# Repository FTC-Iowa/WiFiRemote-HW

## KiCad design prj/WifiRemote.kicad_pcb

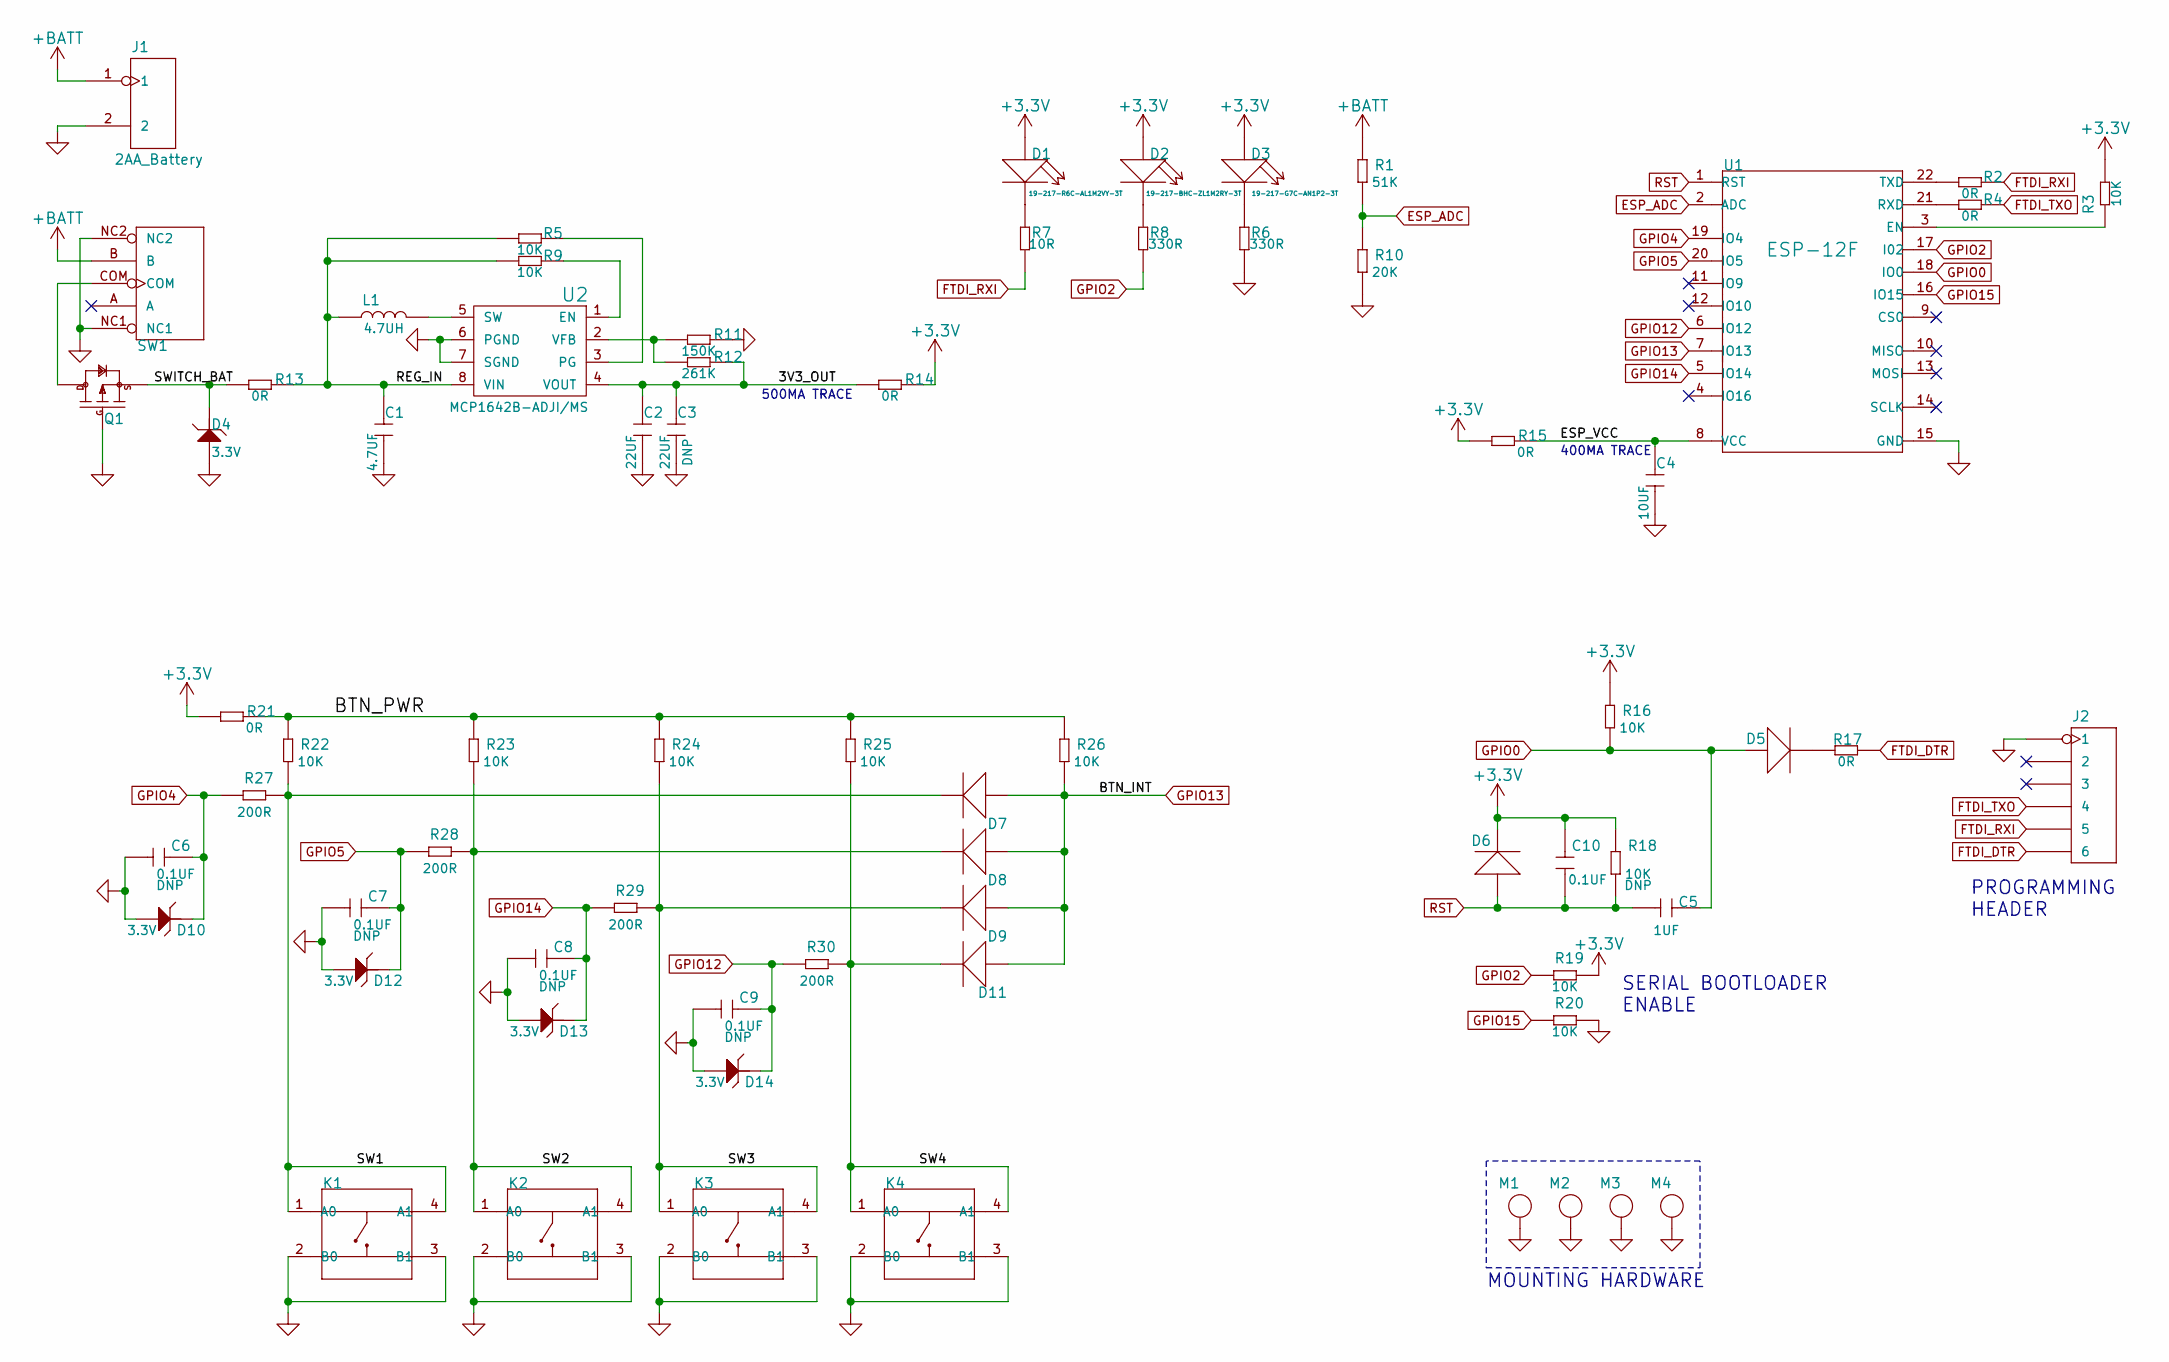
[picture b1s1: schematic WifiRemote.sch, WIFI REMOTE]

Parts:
C1: CERAMIC-4.7UF-10V-10%-X5R_0603_; C0603; MPN CC0603KRX5R6BB475
C2, C3: CERAMIC-22UF-6.3V-20%-X5R_0805_; C0805; MPN CC0805MKX5R5BB226
C4: CERAMIC-10UF-10V-10%-X5R_0603_; C0603; MPN CC0603KRX5R6BB106
C5: CERAMIC-1UF-25V-10%-X7R_0603_; C0603; MPN CC0603KRX7R8BB105
C6, C7, C8, C9, C10: CERAMIC-100NF-50V-10%-X7R_0603_; C0603; MPN CC0603KRX7R9BB104
D1: LED-SMD-RED-DIFFUSED_0603_; LED-0603; MPN 19-217-R6C-AL1M2VY-3T
D2: SMD-LED-CLEAR-BLUE_0603_; LED-0603; MPN 19-217-BHC-ZL1M2RY-3T
D3: SMD-LED-CLEAR-GREEN_0603_; LED-0603; MPN 19-217-G7C-AN1P2-3T
D4, D10, D12, D13, D14: SMD-Diode-TVS-3.3VMW-15V-SOD-523; SOD-523_IMPROVED; MPN CJ;CESD3V3D5
D5, D6, D7, D8, D9, D11: SMD-DIODE-SCHOTTKY-20V-1A_SOD-123_; SOD-123; MPN B5819W
J1: 2AA_Battery; header_1x2; MPN BH-321-1A
J2: DIP-BLACK-MALE-HEADER_6P-2.54_; H6-2.54; MPN P125-1106A1BS116A1
K1, K2, K3, K4: DIP-SWITCH-TACTILE-SPST-NO_TS-1109_4P-D6.0MM_; SW4-6.0X6.0X5.0MM
L1: SMD-Inductor-4.7uH-20%-L0420; ICEE_Inductor_SPD3D16-4R7M; MPN SPD3D16-4R7M
M1, M2, M3, M4: Mechanical_Mount; mounting_panhead6_5mm
Q1: SMD-MOSFET-P-CH-20V-2A-FDN340P_SOT-23_; SOT-23; MPN FDN340P
R1: SMD-RES-51K-5%-1_10W_0603_; R0603; MPN RC0603JR-0751KL
R2, R4, R13, R14, R15, R17, R21: SMD-RES-0R-5%-1_10W_0603_; R0603; MPN RC0603JR-070RL
R3, R16, R18, R19, R20, R22, R23, R24, R25, R26: SMD-RES-10K-5%-1_10W_0603_; R0603; MPN RC0603JR-0710KL
R5, R9: SMD-RES-10K-1%-1_10W_0603_; R0603; MPN RC0603FR-0710KL
R6, R8: SMD-RES-330R-1%-1_10W_0603_; R0603; MPN RC0603FR-07330RL
R7: SMD-RES-10R-5%-1_10W_0603_; R0603; MPN RC0603JR-0710RL
R10: SMD-RES-20K-1%-1_10W_0603_; R0603; MPN RC0603FR-0720KL
R11: SMD-RES-150K-1%-1_10W_0603_; R0603; MPN RC0603FR-07150KL
R12: SMD-RES-261K-1%-1_10W_0603_; R0603; MPN CRCW0603261KFKEA
R27, R28, R29, R30: SMD-RES-200R-5%-1_10W_0603_; R0603; MPN RC0603JR-07200RL
SW1: DIP-TOGGLE-SWITCH-ON-ON_3+2P-8.8X4.6MM_-90D; SW5-2.0-8.8X4.4X4.7MM-90D; MPN 3P-2.0-90D3P-2.0-90D-REINFORCE
U1: CONTROLLER-ESP8266; ESP-12F_SMT_22PIN; PART NUMBER ESP-12F
U2: BOOST-MCP1642B-ADJI/MC-MSOP8; MSOP-8_3x3mm_Pitch0.65mm; PART NUMBER MCP1642B-ADJI/MS

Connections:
+3V3: C10.1, D1.+, D2.+, D3.+, D6.-, R3.1, R14.1, R15.2, R16.1, R18.1, R19.2, R21.2
+BATT: J1.1, R1.1, SW1.B
/3V3_OUT: C2.1, C3.1, R12.1, R14.2, U2.4 (VOUT)
/BTN_PWR: R21.1, R22.1, R23.1, R24.1, R25.1, R26.1
/ESP_VCC: C4.1, R15.1, U1.8 (VCC)
/REG_IN: C1.1, L1.1, R5.2, R9.2, R13.1, U2.8 (VIN)
/SW1: D7.-, K1.1 (A0), K1.4 (A1), R22.2, R27.2
/SW2: D8.-, K2.1 (A0), K2.4 (A1), R23.2, R28.2
/SW3: D9.-, K3.1 (A0), K3.4 (A1), R24.2, R29.2
/SW4: D11.-, K4.1 (A0), K4.4 (A1), R25.2, R30.2
/SWITCH_BAT: D4.1, Q1.2 (S), R13.2
ESP_ADC: R1.2, R10.1, U1.2 (ADC)
FTDI_DTR: J2.6, R17.1
FTDI_RXI: J2.5, R2.1, R7.2
FTDI_TXO: J2.4, R4.1
GNDD: C1.2, C2.2, C3.2, C4.2, C6.1, C7.1, C8.1, C9.1, D4.2, D10.2, D12.2, D13.2, D14.2, J1.2, J2.1, K1.2 (B0), K1.3 (B1), K2.2 (B0), K2.3 (B1), K3.2 (B0), K3.3 (B1), K4.2 (B0), K4.3 (B1), M1.1, M2.1, M3.1, M4.1, Q1.1 (G), R6.2, R10.2, R11.1, R20.2, SW1.NC1, SW1.NC2, U1.15 (GND), U2.6 (PGND), U2.7 (SGND)
GPIO0: C5.2, D5.+, R16.2, U1.18 (IO0)
GPIO2: R8.2, R19.1, U1.17 (I02)
GPIO4: C6.2, D10.1, R27.1, U1.19 (IO4)
GPIO5: C7.2, D12.1, R28.1, U1.20 (IO5)
GPIO12: C9.2, D14.1, R30.1, U1.6 (IO12)
GPIO13: D7.+, D8.+, D9.+, D11.+, R26.2, U1.7 (IO13)
GPIO14: C8.2, D13.1, R29.1, U1.5 (IO14)
GPIO15: R20.1, U1.16 (IO15)
unnamed: D1.-, R7.1
unnamed: D2.-, R8.1
unnamed: D3.-, R6.1
unnamed: D5.-, R17.2
unnamed: L1.2, U2.5 (SW)
unnamed: Q1.3 (D), SW1.COM
unnamed: R2.2, U1.22 (TXD)
unnamed: R3.2, U1.3 (EN)
unnamed: R4.2, U1.21 (RXD)
unnamed: R5.1, U2.3 (PG)
unnamed: R9.1, U2.1 (EN)
unnamed: R11.2, R12.2, U2.2 (VFB)
RST: C5.1, C10.2, D6.+, R18.2, U1.1 (RST)

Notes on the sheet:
PROGRAMMING HEADER
SERIAL BOOTLOADER ENABLE
500MA TRACE
400MA TRACE
MOUNTING HARDWARE

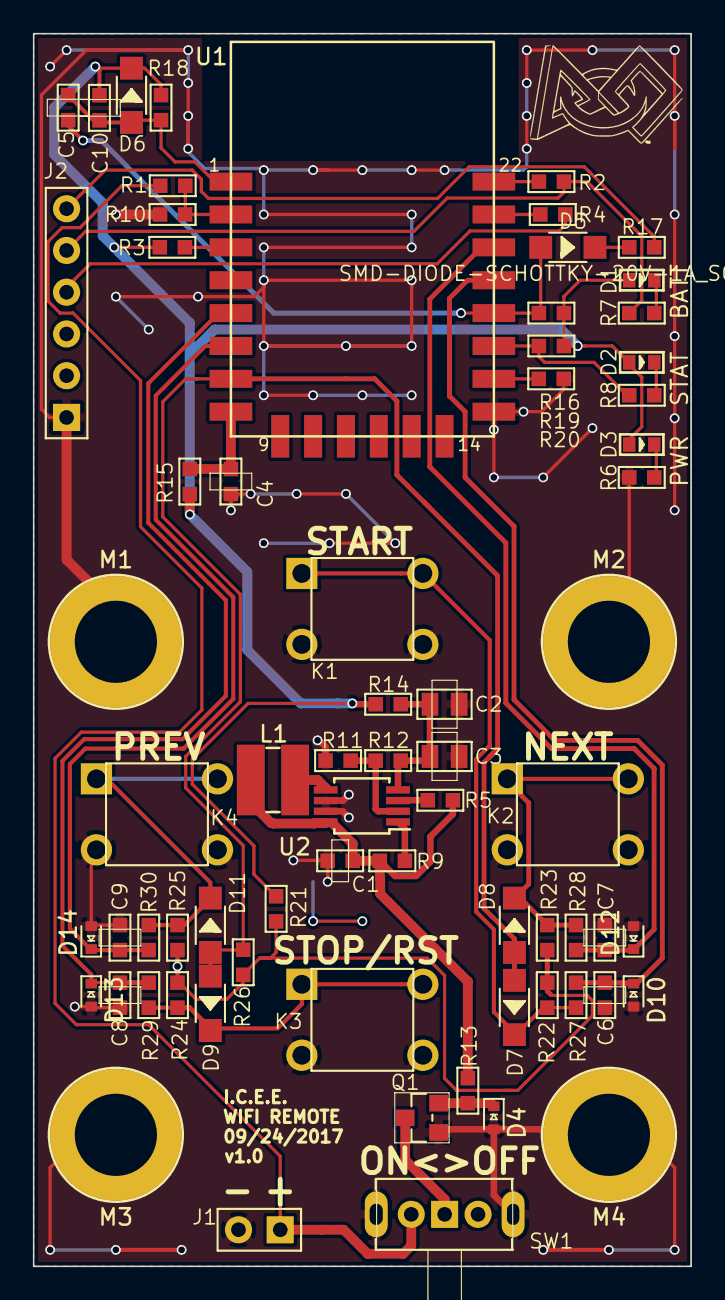
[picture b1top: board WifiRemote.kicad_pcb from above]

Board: 2 copper layers, 40.0 x 75.0 mm, 69 parts (0 on the bottom side), 37 nets.

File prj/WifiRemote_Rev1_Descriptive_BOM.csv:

Component,Description,Part,Designators,Footprint,SKU,MPN,PLACE,Cost,Quantity Per PCB,Cost Per PCB
1,,CERAMIC-100NF-50V-10%-X7R_0603_,C6 C7 C8 C9,C0603,302010138,CC0603KRX7R9BB104,DNP,$0.01 ,4,$0.00 
2,,CERAMIC-10UF-10V-10%-X5R_0603_,C4,C0603,302010103,CC0603KRX5R6BB106,,$0.02 ,1,$0.02 
3,,CERAMIC-1UF-25V-10%-X7R_0603_,C5,C0603,302010139,CC0603KRX7R8BB105,,$0.01 ,1,$0.01 
4,,CERAMIC-22UF-6.3V-20%-X5R_0805_,C2,C0805,302010171,CC0805MKX5R5BB226,,$0.02 ,1,$0.02 
5,,CERAMIC-22UF-6.3V-20%-X5R_0805_,C3,C0805,302010171,CC0805MKX5R5BB226,DNP,$0.02 ,1,$0.00 
6,,CERAMIC-4.7UF-10V-10%-X5R_0603_,C1,C0603,302010111,CC0603KRX5R6BB475,,$0.01 ,1,$0.01 
7,,LED-SMD-RED-DIFFUSED_0603_,D1,LED-0603,304090042,19-217-R6C-AL1M2VY-3T,,$0.01 ,1,$0.01 
8,,SMD-DIODE-SCHOTTKY-20V-1A_SOD-123_,D5 D6 D7 D8 D9 D11,SOD-123,304020034,B5819W,,$0.02 ,6,$0.12 
9,,SMD-Diode-TVS-3.3VMW-15V-SOD-523,D4 D10 D12 D13 D14,SOD-523,304060054,CJ;CESD3V3D5,,$0.02 ,5,$0.10 
10,,SMD-LED-CLEAR-BLUE_0603_,D2,LED-0603,304090045,19-217-BHC-ZL1M2RY-3T,,$0.01 ,1,$0.01 
11,,SMD-LED-CLEAR-GREEN_0603_,D3,LED-0603,304090043,19-217-G7C-AN1P2-3T,,$0.01 ,1,$0.01 
12,,2AA_Battery,J1,header_1x2,320180001,BH-321-1A,,$0.23 ,1,$0.23 
13,,DIP-BLACK-MALE-HEADER_6P-2.54_,J2,H6-2.54,320020078,P125-1106A1BS116A1,,$0.01 ,1,$0.01 
14,,DIP-SWITCH-TACTILE-SPST-NO_TS-1109_4P-D6.0MM_,K1 K2 K3 K4,SW4-6.0X6.0X5.0MM,311020024,TS-1109,,$0.01 ,4,$0.04 
15,,SMD-Inductor-4.7uH-20%-L0420,L1,L0805,303010015,SPD3D16-4R7M,,$0.19 ,1,$0.19 
16,,Mechanical_Mount,M1 M2 M3 M4,mounting_panhead6_5mm,N/A,N/A,DNP,$0.00 ,4,$0.00 
17,,SMD-MOSFET-P-CH-20V-2A-FDN340P_SOT-23_,Q1,SOT-23,305030026,FDN340P,,$0.12 ,1,$0.12 
18,,SMD-RES-0R-5%-1_10W_0603_,R2 R4 R13 R14 R15 R17 R21,R0603,301010292,RC0603JR-070RL,,$0.01 ,7,$0.07 
19,,SMD-RES-10K-1%-1_10W_0603_,R5 R9,R0603,301010299,RC0603FR-0710KL,,$0.01 ,2,$0.02 
20,,SMD-RES-10K-5%-1_10W_0603_,R3 R16 R19 R20 R22 R23 R24 R25 R26,R0603,301010293,RC0603JR-0710KL,,$0.01 ,9,$0.09 
21,,SMD-RES-10K-5%-1_10W_0603_,R18,R0603,301010293,RC0603JR-0710KL,DNP,$0.01 ,1,$0.00 
22,,SMD-RES-10R-5%-1_10W_0603_,R6 R7 R8,R0603,301010096,RC0603JR-0710RL,,$0.01 ,3,$0.03 
23,,SMD-RES-150K-1%-1_10W_0603_,R11,R0603,301010205,RC0603FR-07150KL,,$0.01 ,1,$0.01 
24,,SMD-RES-200R-5%-1_10W_0603_,R27 R28 R29 R30,R0603,301010218,RC0603JR-07200RL,,$0.01 ,4,$0.04 
25,,SMD-RES-20K-1%-1_10W_0603_,R10,R0603,301010288,RC0603FR-0720KL,,$0.01 ,1,$0.01 
26,,SMD-RES-261K-1%-1_10W_0603_,R12,R0603,,CRCW0603261KFKEA,,$0.04 ,1,$0.04 
27,,SMD-RES-51K-5%-1_10W_0603_,R1,R0603,301010145,RC0603JR-0751KL,,$0.01 ,1,$0.01 
28,,DIP-TOGGLE-SWITCH-ON-ON_3+2P-8.8X4.6MM_-90D,SW1,SW5-2.0-8.8X4.4X4.7MM-90D,311030008,3P-2.0-90D3P-2.0-90D-REINFORCE,,$0.01 ,1,$0.01 
29,,BOOST-MCP1642B-ADJI/MC-MSOP8,U2,MSOP-8_3x3mm_Pitch0.65mm,,MCP1642B-ADJI/MS,,$0.98 ,1,$0.98 
30,,CONTROLLER-ESP8266,U1,ESP-12F_SMT_22PIN,317060163,,,$2.14 ,1,$2.14 
,,,,,,,,,,
,,,,,,,,,,
,,,,,,,,,,
Component Groups:,30,,,,,,,,,
Component Count:,68,,,,,,,,,
Fitted Components:,68,,,,,,,,,
Number of PCBs:,10,,,,,,,,,
Total components:,680,,,,,,,,,
Total Cost:,$4.35 ,,,,,,,,,
Schematic Version:,1,,,,,,,,,
Schematic Date:,9/10/2017,,,,,,,,,
BoM Date:,9/24/2017 14:47,,,,,,,,,

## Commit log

2017-08-31 Added hello world
2017-08-31 removed test file
2017-08-31 added start message
2017-08-31 Add text file
2017-08-31 added test file
2017-08-31 testing the graph
2017-08-31 Removed all test files
2017-08-31 Added project files and folder structure
2017-08-31 Added libraries to project
2017-08-31 Changed lib refereences
2017-09-02 Began initial schematic development
2017-09-03 Completed power supply design
2017-09-03 Added ESP and FTDI interface in Schematic
2017-09-05 Added push buttons, ESP programming lines, and battery voltage monitoring
2017-09-05 Added power switch
2017-09-09 Added library files for resistors, caps, inductors, and ESP8266
2017-09-09 Added resistors and boost regulator libraries
2017-09-09 Added libraries and several components to schematic
2017-09-09 Added inductors library and wired boost regulator
2017-09-09 Added 3.3V TVS diode
2017-09-09 Rev1 schematic all components placed and wired
2017-09-10 Arranged designators, Added text descriptions, changed border template
2017-09-10 Added cache.lib to the project
2017-09-10 Added pdf
2017-09-10 Added IC and capacitor .dcm files
2017-09-10 Added cache-lib to project libraries
2017-09-10 Added footprints for all components, modified some sch libraries to add BOM info
2017-09-11 Started layout
2017-09-12 Updated ADC input for 3V input (2x AA's)
2017-09-13 Added battery monitoring LED, changed ADC resistor divider, and added ESD + reverse polarity protection on battery
2017-09-15 Added button debounce, rev polarity prot, updated ESP-12F, added red LED, updated ADC resistor values
2017-09-15 Changed to dynamic libary location
2017-09-15 Changed to dynamic libary location fixed last two
2017-09-15 Updated footprints and removed ESP-12F incorrect footprint
2017-09-15 Fixed regulator pinout, added mechanical mounts to schematic
2017-09-15 Added mounting hole footprint
2017-09-15 First rev of layout
2017-09-18 Hid all value descriptors in layout
2017-09-19 Finished component layout of regulator
2017-09-19 Swapped J1 header (Battery) and J2 header (Programming)
2017-09-19 Routing has begun
2017-09-20 Swapped LED colors, changed mechanical mounts, fixed schematic TVS diode pins, edited button connections to ESP
2017-09-21 Changed button GPIO association and updated mechanical mount pin
2017-09-21 Updated TVS diode pinout
2017-09-21 Added new SOD-523 diode footprint to ICEE library
2017-09-21 Updated lib table to fix local reference issue
2017-09-21 Completed routing awaiting review
2017-09-21 Updated references
2017-09-21 Swapped D2 and D3
2017-09-24 Swapped D1 and D2 for layout
2017-09-24 Updated battery connector
2017-09-24 Added 2 pin header footprint
2017-09-24 Added footprint for header_1x2
2017-09-24 changes stemming from layout review
2017-09-24 Swapped diode packages
2017-09-24 Updates to diodes
2017-09-24 Changed LED packages to 0603
2017-09-24 Changed LED annotations
2017-09-24 Updated gitignore to allow .csv files and added Rev1 BOM
2017-09-24 Added PLACE field column
2017-09-24 Added descriptive BOM with associated costs
2017-09-24 Added silkscreen logos
2017-09-24 Added ftc logos to library
2017-09-24 Added gerber files
2017-09-25 Updated BOM
2017-09-25 Updated BOM to follow all Seeed reqs
2017-09-25 Updated gerber files for ordering
2017-09-25 Added slotted holes to switch
2017-09-26 Removed non Seeed OPL parts from orderable BOM
2017-10-24 Updated Schematic PDF
2017-12-10 Changed R6 and R8 to 330R and added C10
2017-12-10 Updated silk screen issue and changed inductor footprint
2017-12-10 Replaced TVS Diode footprint to included polarity marker
